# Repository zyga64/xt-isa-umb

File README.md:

### Simple UMB memory expansion for IBM PC (XT) and clones.

With this card, you can add 128 kB of continuous UMB memory in the D0000 - EFFFF area, or only 64 kB in the D0000 - DFFFF or E0000 - EFFFF areas. 

* Original schematic diagram was drawn by Ruud Baltissen (VCF forum thread): https://forum.vcfed.org/index.php?threads/loading-dos-high-on-a-xt.32320/
* The idea for the printed circuit board layout borrowed from Adrian Black: https://github.com/misterblack1/isa-ram-expansion
* 8 bit ISA footprint from Sergey Kiselev: https://github.com/skiselev/my_kicad_library

Diagram/PCB drawn by me in KiCad 9.0, the only minor change from Ruud's schematic is the addition of a 74LS245 buffer for the data bus (as done by Adrian and in the Lo-tech 1MB RAM Board https://www.lo-tech.co.uk/wiki/Lo-tech_1MB_RAM_Board).

## Bill Of Materials

Reference      | Quantity    | Value                    
---------------|-------------|--------------------------
U1             | 1           | 74HCT138                  
U2             | 1           | 74HCT08                   
U3             | 1           | AS6C1008 (or another compatible 128k x 8bit SRAM)
U4             | 1           | 74HCT245                  
C6             | 1           | 47uF /16V                 
C1, C2, C3, C4 | 4           | 100nF                     
JP1, JP2       | 2           | 1x02 male through-hole pin-header 2.54mm
R1, R2         | 2           | 15k / 0.125W   (pull-up resistors - 10k will also be fine)

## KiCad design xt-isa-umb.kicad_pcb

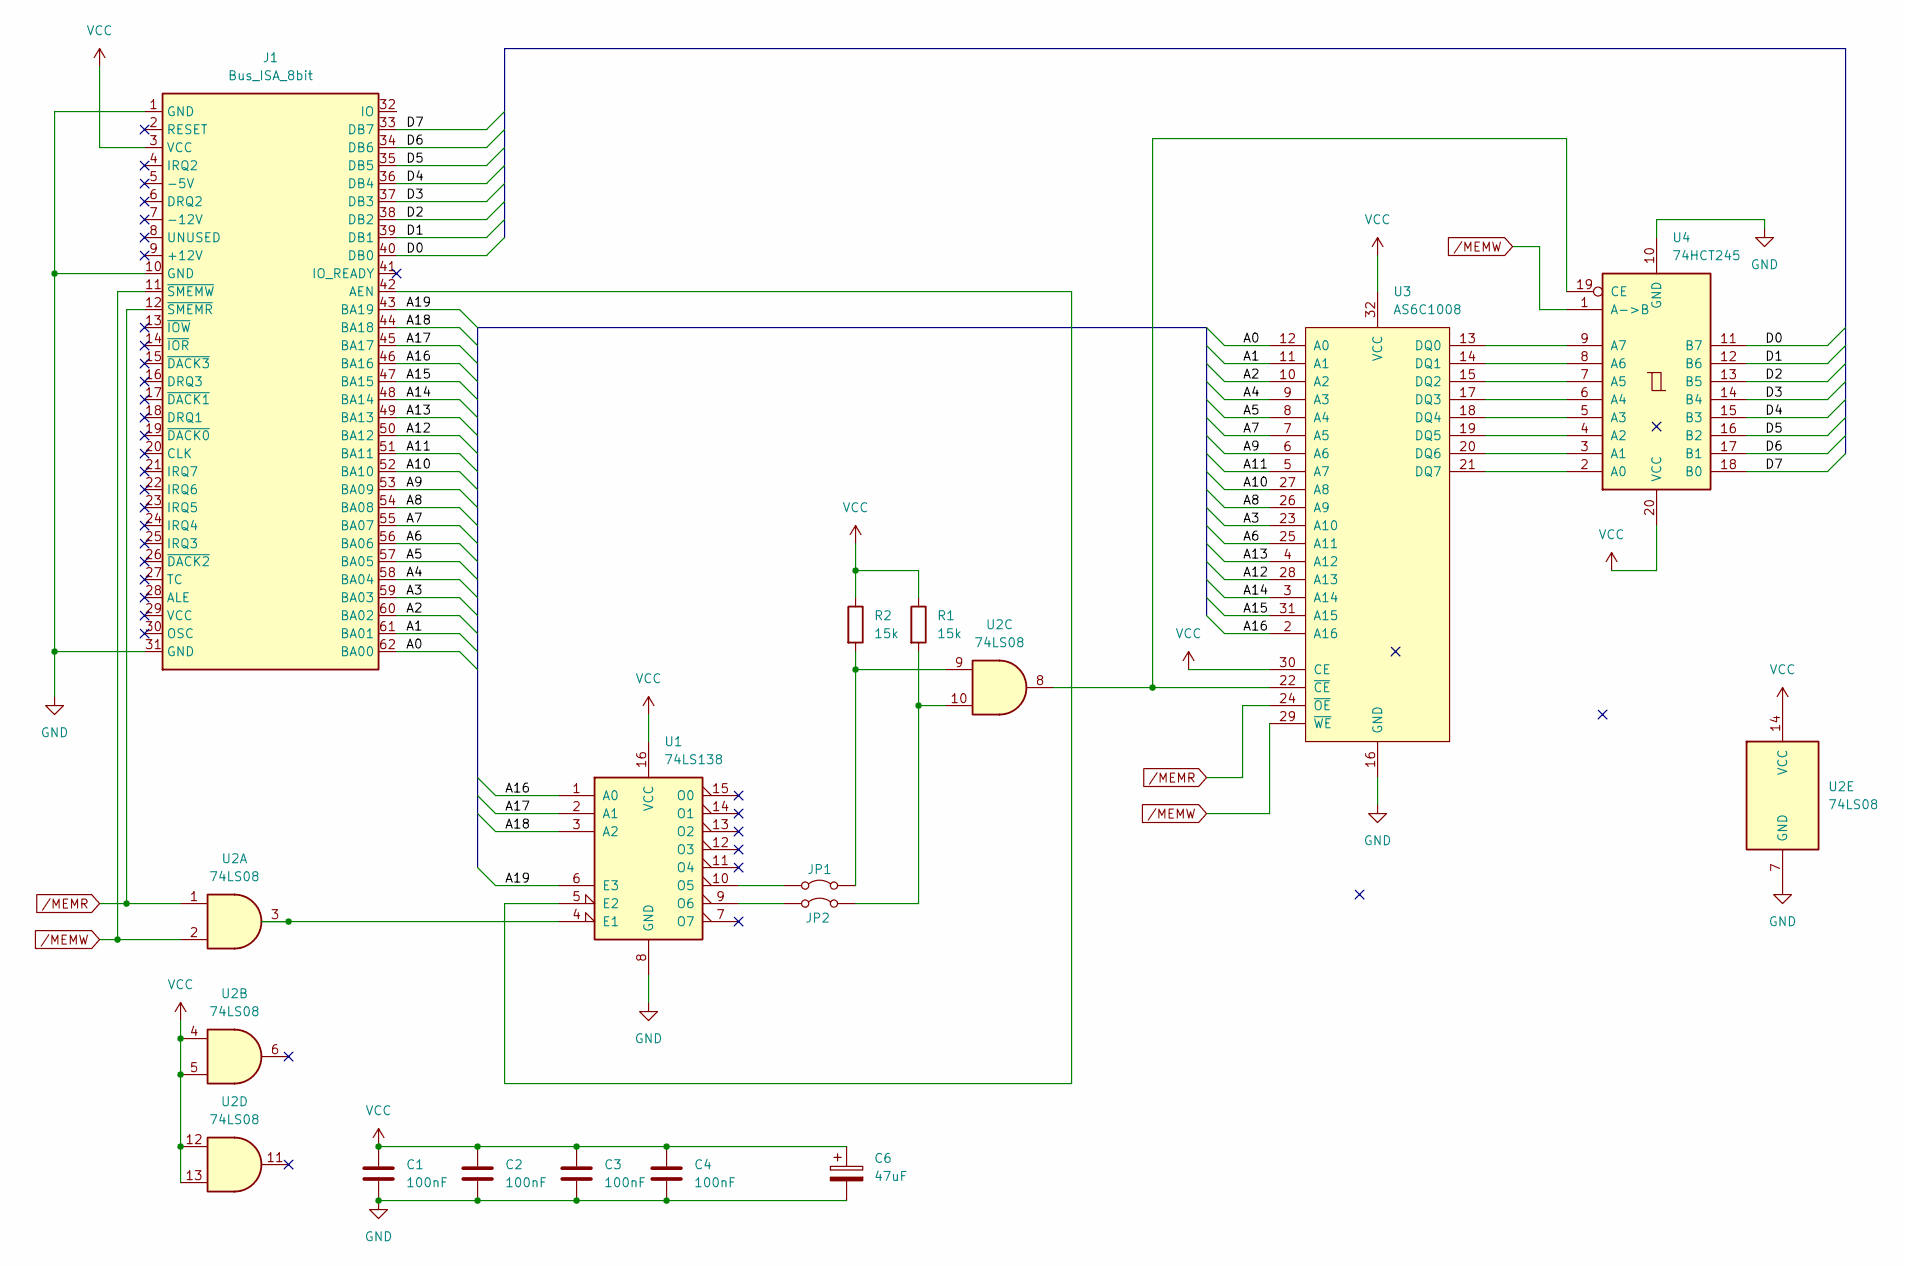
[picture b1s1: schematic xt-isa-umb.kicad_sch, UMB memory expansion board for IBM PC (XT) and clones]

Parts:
C1, C2, C3, C4: 100nF; C_Disc_D4.7mm_W2.5mm_P5.00mm
C6: 47uF; CP_Radial_D4.0mm_P2.00mm
J1: Bus_ISA_8bit; Conn_Edge_PCB_ISA8
JP1, JP2: Jumper_2_Bridged; PinHeader_1x02_P2.54mm_Vertical
R1, R2: 15k; R_Axial_DIN0204_L3.6mm_D1.6mm_P7.62mm_Horizontal
U1: 74LS138; DIP-16_W7.62mm
U2: 74LS08; DIP-14_W7.62mm
U3: AS6C1008; DIP-32_W15.24mm
U4: 74HCT245; DIP-20_W7.62mm

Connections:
/A0: J1.62 (BA00), U3.12 (A0)
/A1: J1.61 (BA01), U3.11 (A1)
/A2: J1.60 (BA02), U3.10 (A2)
/A3: J1.59 (BA03), U3.23 (A10)
/A4: J1.58 (BA04), U3.9 (A3)
/A5: J1.57 (BA05), U3.8 (A4)
/A6: J1.56 (BA06), U3.25 (A11)
/A7: J1.55 (BA07), U3.7 (A5)
/A8: J1.54 (BA08), U3.26 (A9)
/A9: J1.53 (BA09), U3.6 (A6)
/A10: J1.52 (BA10), U3.27 (A8)
/A11: J1.51 (BA11), U3.5 (A7)
/A12: J1.50 (BA12), U3.28 (A13)
/A13: J1.49 (BA13), U3.4 (A12)
/A14: J1.48 (BA14), U3.3 (A14)
/A15: J1.47 (BA15), U3.31 (A15)
/A16: J1.46 (BA16), U1.1 (A0), U3.2 (A16)
/A17: J1.45 (BA17), U1.2 (A1)
/A18: J1.44 (BA18), U1.3 (A2)
/A19: J1.43 (BA19), U1.6 (E3)
/D0: J1.40 (DB0), U4.11 (B7)
/D1: J1.39 (DB1), U4.12 (B6)
/D2: J1.38 (DB2), U4.13 (B5)
/D3: J1.37 (DB3), U4.14 (B4)
/D4: J1.36 (DB4), U4.15 (B3)
/D5: J1.35 (DB5), U4.16 (B2)
/D6: J1.34 (DB6), U4.17 (B1)
/D7: J1.33 (DB7), U4.18 (B0)
GND: C1.2, C2.2, C3.2, C4.2, C6.2, J1.1 (GND), J1.10 (GND), J1.31 (GND), U1.8 (GND), U2.7 (GND), U3.16 (GND), U4.10 (GND)
unnamed: J1.42 (AEN), U1.5 (E2)
unnamed: JP1.1 (A), U1.10 (O5)
unnamed: JP1.2 (B), R2.2, U2.9
unnamed: JP2.1 (A), U1.9 (O6)
unnamed: JP2.2 (B), R1.2, U2.10
unnamed: U1.4 (E1), U2.3
unnamed: U3.13 (DQ0), U4.9 (A7)
unnamed: U3.14 (DQ1), U4.8 (A6)
unnamed: U3.15 (DQ2), U4.7 (A5)
unnamed: U3.17 (DQ3), U4.6 (A4)
unnamed: U3.18 (DQ4), U4.5 (A3)
unnamed: U3.19 (DQ5), U4.4 (A2)
unnamed: U3.20 (DQ6), U4.3 (A1)
unnamed: U3.21 (DQ7), U4.2 (A0)
unnamed: U2.8, U3.22 (~CE), U4.19 (CE)
VCC: C1.1, C2.1, C3.1, C4.1, C6.1, J1.3 (VCC), R1.1, R2.1, U1.16 (VCC), U2.4, U2.5, U2.12, U2.13, U2.14 (VCC), U3.30 (CE), U3.32 (VCC), U4.20 (VCC)
/MEMR: J1.12 (~SMEMR), U2.1, U3.24 (~OE)
/MEMW: J1.11 (~SMEMW), U2.2, U3.29 (~WE), U4.1 (A->B)

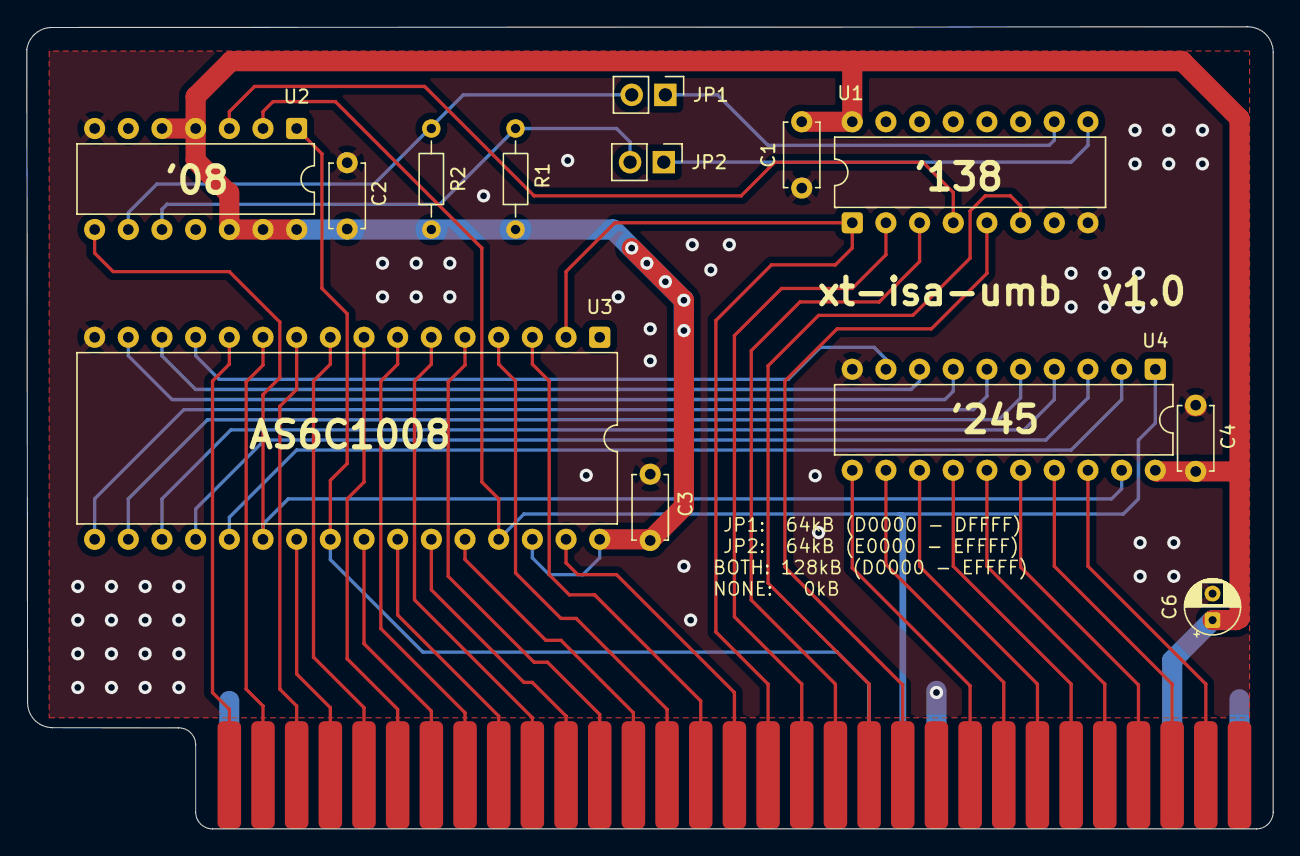
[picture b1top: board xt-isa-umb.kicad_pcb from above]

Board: 2 copper layers, 94.0 x 60.5 mm, 14 parts (0 on the bottom side), 47 nets.

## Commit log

2026-01-03 added 3D view of PCB
2026-01-03 image resize
2026-01-03 Create README
    Added a README with details about the UMB memory expansion card.
2026-01-03 Corrected mistake in readme
2026-01-04 Modify capacitors and VCC/GND track placement
2026-01-04 3d_view image update
2026-01-04 Further VCC/GND tracks modification
2026-01-21 Add GND fill zone.
2026-01-22 Add top GND fill zone
2026-01-22 Add gerber files
2026-02-04 Modify components designation, add thermal reliefs, change C6 orientation
2026-02-04 Added images
2026-02-04 Resize images
2026-02-04 Revise README with new images and BOM
    Updated images and added Bill Of Materials section.
2026-02-04 Update gerbers
2026-02-04 remove image from root folder
